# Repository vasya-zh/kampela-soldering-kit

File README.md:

# kampela-soldering-kit

## Overview

Do-it-yourself kit to make your own, fully-functional Kampela signer

## Features
- Easy to solder and self-assembly transaction signer kit
- NFC-powered batteryless operation
- secure vault implemented in EFM32PG23 MCU
- 2.7" ePaper display with touchscreen
- you can fill the assembled kit with transparent UV-cured glue after assembly and tests to make it unchangeable

## Why did we create this?

We want to make kampela design as transparent, verifiable and open-source as possible, that's simple.

## Components

Kampela solder kit consists of several off-the-shelf modules, simple electronic components and 3d printed parts:

**Modules:**
- 1pc - [Lisko A1](https://github.com/vasya-zh/Lisko) EFM32 devboard
- 1pc - [SparkFun BabyBuck 3.3V](https://www.sparkfun.com/products/18357) - step-down converter module 
- 1pc - [Olimex BB-PWR-3608](https://www.olimex.com/Products/Breadboarding/BB-PWR-3608/open-source-hardware) - step-up converter module 12V/24V
- 1pc - [Touch-6pin-adapter](https://github.com/vasya-zh/kampela-soldering-kit/tree/v2/kicad/touch-6pin-adapter) - 6-pin 0.5mm pitch FPC cable adapter for i2c touch screens
- 1pc - [NFC tag](https://github.com/vasya-zh/kampela-soldering-kit/tree/v2/kicad/tag) PCB with M24SR02 NFC EEPROM chip onboard

**PCBs:**
- 1pc - [Base-board](kicad/base-board/) - main Kampela soldering kit PCB
- 1pc - [flex nfc antenna](https://github.com/vasya-zh/kampela-soldering-kit/tree/v2/kicad/flex-coil8/production) PCB

**3d printed parts:**
- 1pc - [Solder kit enclosure](3d-models/solder-kit-enclosure.stl), 3d printed with transparent SLA resin
- 1pc - [NFC tag enclosure](3d-models/nfc-tag-enclosure.stl), 3d printed with transparent SLA resin

**Electronic components:**
- 1pc - [GDEY027T91-T01](https://www.good-display.com/product/259.html) ePaper display
- 1pc - [TLC372IP](https://www.ti.com/lit/ds/symlink/tlc372.pdf?ts=1715700121988&ref_url=https%253A%252F%252Fwww.google.com%252F) - comparator in DIP8 package
- 1pc - [L78L24](https://www.st.com/resource/en/datasheet/l78l.pdf) - 24V linear voltage regulator in TO-92 package 
- 6pcs - [1N5819](https://www.vishay.com/docs/88525/1n5817.pdf) schottky diode 40V 1A
- 1pc - [1N4743A](https://www.nexperia.com/products/diodes/zener-diodes/1N4743A.html) 13V 1W Zener diode
- 1pc - [3mm red LED](https://www.mouser.fi/ProductDetail/Vishay-Semiconductors/TLDR4900?qs=Lv5%252BaqTFJEN9M2YxsERGfA%3D%3D) for NFC field presence indication 

**Capacitors:**
- 1pc - [15pF 50V](https://www.lcsc.com/product-detail/Multilayer-Ceramic-Capacitors-MLCC-Leaded_TORCH-CC4-0805-CG-50V-15pF-J_C123158.html) ceramic capacitor
- 2pcs - [100pF 50V](https://www.lcsc.com/product-detail/Multilayer-Ceramic-Capacitors-MLCC-Leaded_Murata-Electronics-RCE5C2A101J0DBH03A_C1622101.html) ceramic capacitor
- 2pcs - [0.1uF 50V](https://www.lcsc.com/product-detail/Multilayer-Ceramic-Capacitors-MLCC-Leaded_KNSCHA-178MU0006_C5632430.html) ceramic capacitor
- 2pcs - [1uF 50V](https://www.lcsc.com/product-detail/Multilayer-Ceramic-Capacitors-MLCC-Leaded_KNSCHA-178MU0010_C5632434.html) ceramic capacitor
- 1pc - [220uF 25V](https://www.lcsc.com/product-detail/Aluminum-Electrolytic-Capacitors-Leaded_CX-Dongguan-Chengxing-Elec-KM227M025E11RR0VH2FP0_C12450.html) aluminium capacitor d6.3mm\*11mm

**Resistors:**
- 4pcs - [10k 0.125w](https://www.lcsc.com/product-detail/Through-Hole-Resistors_VO-MF1-8W-10K-1-ST26_C2903381.html) resistor
- 6pcs - [47k 0.125w](https://www.lcsc.com/product-detail/Through-Hole-Resistors_Futaba-Elec-RNU18F4702A520NH_C274421.html) resistor
- 1pc - [300k 0.125w](https://www.lcsc.com/product-detail/Through-Hole-Resistors_TyoHM-RN-1-8W-300K-F-T-B-A1_C433482.html) resistor

Complete CSV BOM can be found [here](docs/kampela-soldering-kit-BOM.csv)

## Assembly instructions

Assembly instructions can be found here: [/docs/assembly-manual.md](docs/assembly-manual.md)

> [!Note] 
> Don't fill your assembly with transparent UV adhesive before you fully test it and flash it with the right firmware.  

## Flashing and testing

Flashing and testing instructions can be found here: [/docs/flashing-n-testing.md](docs/flashing-n-testing.md)

## Using your Kampela Solder Kit

You can use your solder kit as a transaction signer with the real [Kampela firmware](https://github.com/Kalapaja/kampela-firmware)

To do that you need to flash it with the latest [binary firmware released](https://github.com/Kalapaja/kampela-firmware/tags) or build it from the [source code](https://github.com/Kalapaja/kampela-firmware)

Or you can make your customized version of the firmware and hardware.

## How to produce your own Kampela Solder Kit

You can get the kit in [kampe.la](https://kampe.la) shop

Or make your kit. To do that you need:
- order PCBs from your favourite PCB manufacturer. Gerber files can be found here: [base-board](https://github.com/vasya-zh/kampela-soldering-kit/tree/v2/kicad/base-board/production), [flex-antenna](https://github.com/vasya-zh/kampela-soldering-kit/tree/v2/kicad/flex-coil8/production)
- order modules and electronic components, see the [full BOM](docs/kampela-soldering-kit-BOM.csv)
- order or print enclosures with transparent SLA resin. STL and STEP files can be found [here](3d-models/)
- if you want you can also make your version of [Lisko A1](https://github.com/vasya-zh/Lisko) board and [FPC adapter](https://github.com/vasya-zh/kampela-soldering-kit/tree/v2/kicad/touch-6pin-adapter) board. Overwise contact [kampela team](https://kampe.la)

## About this design

Schematic PDF diagrams can be found [here](docs/)

KiCad projects can be found [here](kicad/)

This kit was made using only open-source tools:
- [KiCad](https://www.kicad.org/) - for schematics and PCBs
- [FreeCad](https://www.freecad.org/) - for enclosure design
- [Blender](https://www.blender.org/) - for renders and images
- [InkScape](https://inkscape.org/) - for instructions diagrams

## TODO
- ! Change ePaper and touch screen RESET signal polarity in test and release firmware! 

## Contributors

- [Vasilii Zhuravskii](https://github.com/vasya-zh) - solder kit v2 design, schematics, boards design, DFM, docs, tests

- [Yuri Ilin](https://www.youtube.com/@katsuk) - solder kit v1 design, schematics, flasher firmware, EFM32 test firmware in C with E-INK and other features

This project was made at [Alzymologist Oy](https://github.com/alzymologist) as a part of [Kampela](https://kampe.la) project.

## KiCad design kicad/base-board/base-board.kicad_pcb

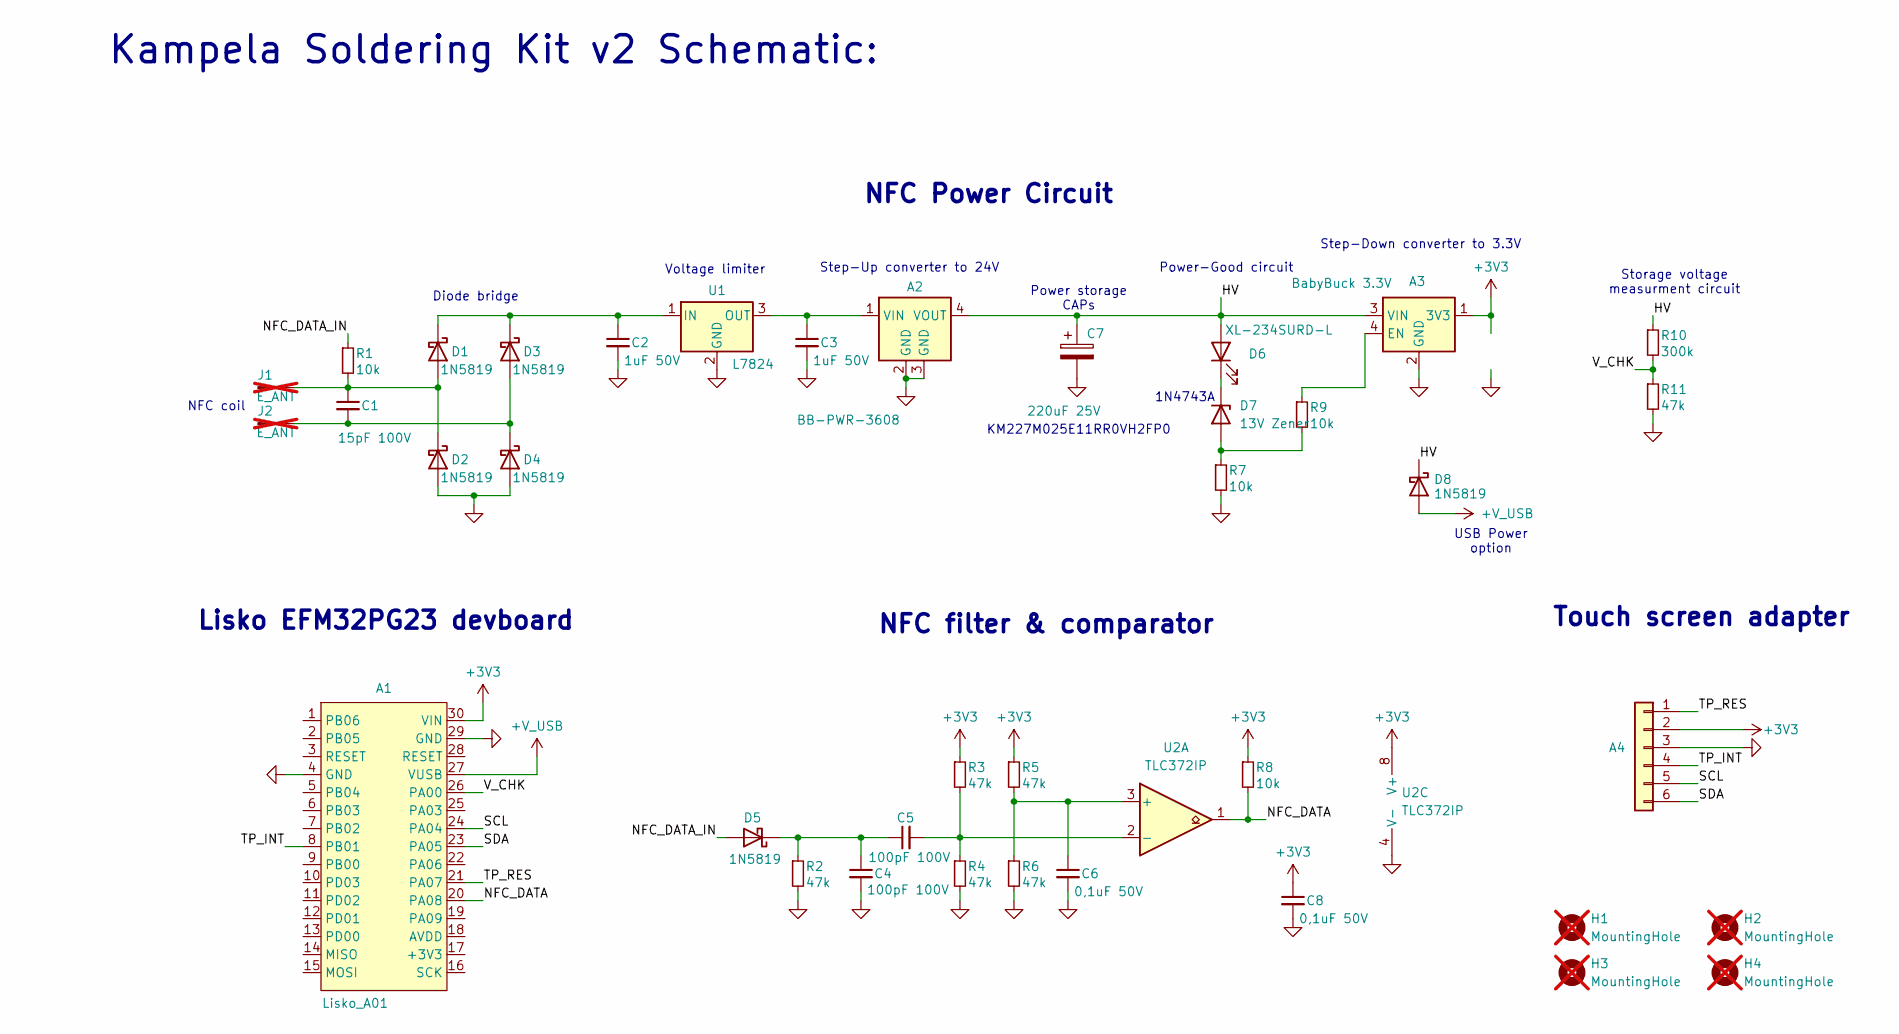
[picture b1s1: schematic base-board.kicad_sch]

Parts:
A1: Lisko_A01; Lisko_A01-DIP-only
A2: BB-PWR-3608; BB-PWR-3608-in-board
A3: BabyBuck 3.3V; SparkFun_BabyBuck_3.3V-in-board
A4: touch-6pin-adapter
C1: 15pF 100V; C_Disc_D5.0mm_W2.5mm_P2.50mm; Mouser Part # 80-C315C150J1G; LCSC Part # C123158
C2, C3: 1uF 50V; C_Disc_D5.0mm_W2.5mm_P2.50mm; Mouser Part # 81-RCER72A105K2DBH3A; LCSC Part # C5632434
C4, C5: 100pF 100V; C_Disc_D5.0mm_W2.5mm_P2.50mm; Mouser Part # 810-FG18C0G2A101JNT6; LCSC Part # C1622101
C6, C8: 0,1uF 50V; C_Disc_D5.0mm_W2.5mm_P2.50mm; Mouser Part # 80-C320C104K2R5TA; LCSC Part # C5632430
C7: 220uF 25V; CAP_RADIAL_6.3_2.5_11_HOR-DIP; Mouser Part # 710-860010473011; LCSC Part # C12450
D1, D2, D3, D4, D5, D8: 1N5819; D_DO-41_SOD81_P7.62mm_Horizontal; Mouser Part # 637-1N5819; LCSC Part # C2474
D6: XL-234SURD-L; LED_Rectangular_W3.0mm_H2.0mm; Mouser Part # 604-WP424IDT; LCSC Part # C5440555
D7: 13V Zener; D_DO-41_SOD81_P7.62mm_Horizontal; Mouser Part # 771-1N4743A-T/R; LCSC Part # C2546
H1, H2, H3, H4: MountingHole; MountingHole_2.1mm; not fitted
J1, J2: E_ANT; Pad_1.8x3; not fitted
R1, R7, R8, R9: 10k; R_Axial_DIN0204_L3.6mm_D1.6mm_P5.08mm_Horizontal; Mouser Part # 303-MF0W8FF1002A20; LCSC Part # C2903381
R2, R3, R4, R5, R6, R11: 47k; R_Axial_DIN0204_L3.6mm_D1.6mm_P5.08mm_Horizontal; Mouser Part # 303-MF0W8FF4702B00; LCSC Part # C274421
R10: 300k; R_Axial_DIN0204_L3.6mm_D1.6mm_P5.08mm_Horizontal; Mouser Part # 71-RN55E3003B; LCSC Part # C433482
U1: L7824; TO-92_Inline; Mouser Part # 863-MC79L24ACPRMG; LCSC Part # C903167
U2: TLC372IP; DIP-8_W7.62mm; Mouser Part # 595-TLC372IP; LCSC Part # C2862094

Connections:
+3V3: A1.30 (VIN), A3.1 (3V3), A4.2, C8.1, R3.1, R5.1, R8.1, U2.8 (V+)
+V_USB: A1.27 (VUSB), D8.2 (A)
/HV: A2.4 (VOUT), A3.3 (VIN), C7.1, D6.2 (A), D8.1 (K), R10.1
/NFC_DATA: A1.20 (PA08), R8.2, U2.1
/NFC_DATA_IN: D5.2 (A), R1.1
/SCL: A1.24 (PA04), A4.5
/SDA: A1.23 (PA05), A4.6
/TP_INT: A1.8 (PB01), A4.4
/TP_RES: A1.21 (PA07), A4.1
/V_CHK: A1.26 (PA00), R10.2, R11.1
GND: A1.4 (GND), A1.29 (GND), A2.2 (GND), A2.3 (GND), A3.2 (GND), A4.3, C2.2, C3.2, C4.2, C6.2, C7.2, C8.2, D2.2 (A), D4.2 (A), R2.2, R4.2, R6.2, R7.2, R11.2, U1.2 (GND), U2.4 (V-)
unnamed: A2.1 (VIN), C3.1, U1.3 (OUT)
unnamed: A3.4 (EN), R9.1
unnamed: C1.1, D1.2 (A), D2.1 (K), J1.1, R1.2
unnamed: C2.1, D1.1 (K), D3.1 (K), U1.1 (IN)
unnamed: C1.2, D3.2 (A), D4.1 (K), J2.1
unnamed: C4.1, C5.1, D5.1 (K), R2.1
unnamed: D6.1 (K), D7.1 (K)
unnamed: D7.2 (A), R7.1, R9.2
unnamed: C6.1, R5.2, R6.1, U2.3 (+)
unnamed: C5.2, R3.2, R4.1, U2.2 (-)

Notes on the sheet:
1N4743A
Lisko EFM32PG23 devboard
Kampela Soldering Kit v2 Schematic:
NFC Power Circuit
Step-Down converter to 3.3V
KM227M025E11RR0VH2FP0
USB Power option
NFC filter & comparator
Voltage limiter
Storage voltage measurment circuit
Diode bridge
Touch screen adapter
NFC coil
Step-Up converter to 24V
Power-Good circuit
Power storage CAPs

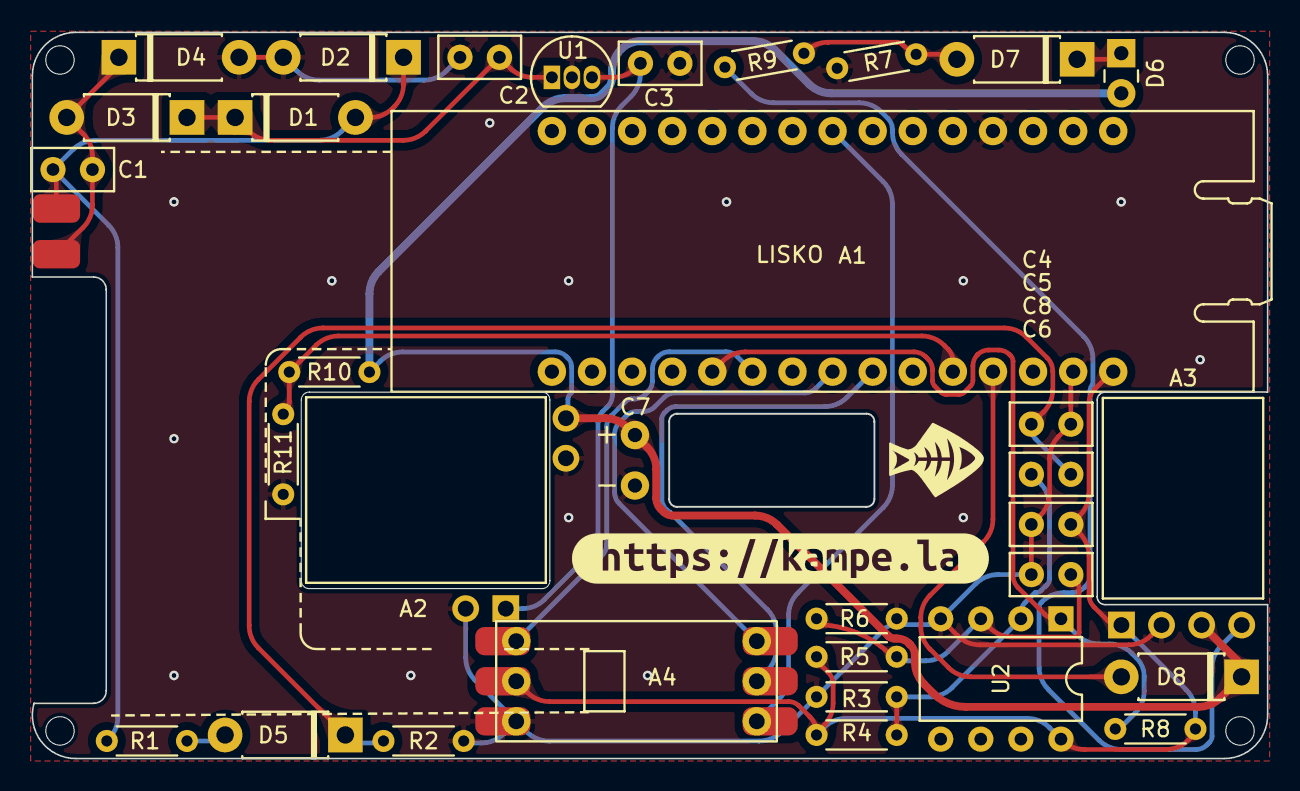
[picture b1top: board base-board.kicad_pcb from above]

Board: 2 copper layers, 78.2 x 46.0 mm, 43 parts (0 on the bottom side), 21 nets.

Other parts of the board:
H2#2, H3#2, H4#2: MountingHole; MountingHole_2.1mm
kibuzzard-6635354C: G***; kibuzzard-6635354C

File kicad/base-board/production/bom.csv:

Designator,Footprint,Quantity,Value,LCSC Part #
A1,Lisko_A01-DIP-only,1,Lisko_A01,-
A2,BB-PWR-3608-in-board,1,BB-PWR-3608,-
A3,SparkFun_BabyBuck_3.3V-in-board,1,BabyBuck 3.3V,-
A4,touch-6pin-adapter,1, ,-
C1,C_Disc_D5.0mm_W2.5mm_P2.50mm,1,15pF 100V,C123158
"C2, C3",C_Disc_D5.0mm_W2.5mm_P2.50mm,2,1uF 50V,C5632434
"C4, C5",C_Disc_D5.0mm_W2.5mm_P2.50mm,2,100pF 100V,C1622101
"C6, C8",C_Disc_D5.0mm_W2.5mm_P2.50mm,2,"0,1uF 50V",C5632430
C7,CAP_RADIAL_6.3_2.5_11_HOR-DIP,1,220uF 25V,C12450
"D1, D2, D3, D4, D5, D8",D_DO-41_SOD81_P7.62mm_Horizontal,6,1N5819,C2474
D6,LED_Rectangular_W3.0mm_H2.0mm,1,XL-234SURD-L,C5440555
D7,D_DO-41_SOD81_P7.62mm_Horizontal,1,13V Zener,C2546
"J1, J2",Pad_1.8x3,2,E_ANT,-
"R1, R7, R8, R9",R_Axial_DIN0204_L3.6mm_D1.6mm_P5.08mm_Horizontal,4,10k,C2903381
R10,R_Axial_DIN0204_L3.6mm_D1.6mm_P5.08mm_Horizontal,1,300k,C433482
"R11, R2, R3, R4, R5, R6",R_Axial_DIN0204_L3.6mm_D1.6mm_P5.08mm_Horizontal,6,47k,C274421
U1,TO-92_Inline,1,L7824,C903167
U2,DIP-8_W7.62mm,1,TLC372IP,C2862094

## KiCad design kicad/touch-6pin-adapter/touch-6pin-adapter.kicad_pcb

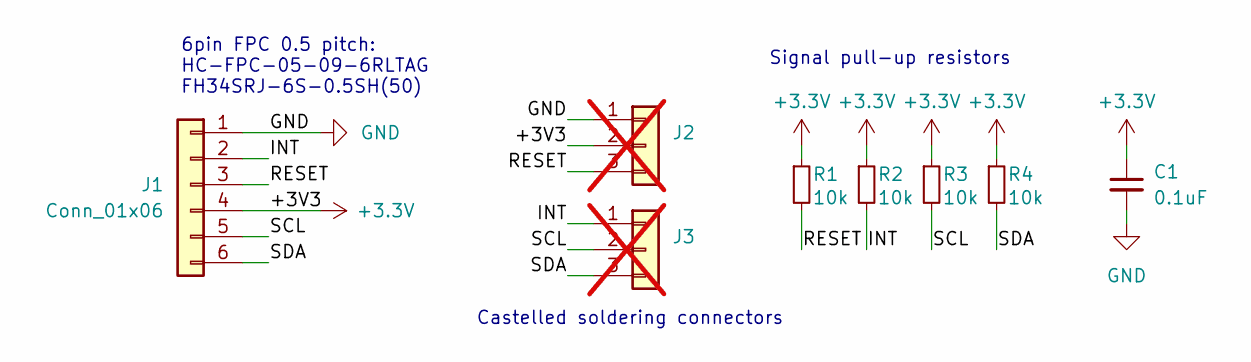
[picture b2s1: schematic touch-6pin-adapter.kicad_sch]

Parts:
C1: 0.1uF; C_0402_1005Metric; LCSC Part # C5142567
J1: Conn_01x06; HRS_FH34SRJ-6S-0.5SH_50_; LCSC Part # C5213748
J2, J3: Conn_01x03; Connector_Castelled_3pin_2.54mm_withVIA; not fitted
R1, R2, R3, R4: 10k; R_0402_1005Metric; LCSC Part # C2906885

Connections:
+3.3V: C1.1, J1.4, J2.2, R1.1, R2.1, R3.1, R4.1
/INT: J1.2, J3.1, R2.2
/RESET: J1.3, J2.3, R1.2
/SCL: J1.5, J3.2, R3.2
/SDA: J1.6, J3.3, R4.2
GND: C1.2, J1.1, J2.1

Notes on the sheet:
Signal pull-up resistors
6pin FPC 0.5 pitch: HC-FPC-05-09-6RLTAG FH34SRJ-6S-0.5SH(50)
Castelled soldering connectors

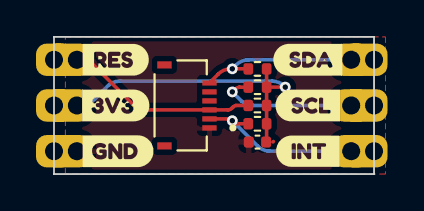
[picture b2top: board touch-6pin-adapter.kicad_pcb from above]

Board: 2 copper layers, 17.8 x 7.6 mm, 14 parts (0 on the bottom side), 6 nets.

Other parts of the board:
kibuzzard-663390A2: G***; kibuzzard-663390A2
kibuzzard-663390A9: G***; kibuzzard-663390A9
kibuzzard-663390E6: G***; kibuzzard-663390E6
kibuzzard-6633914E: G***; kibuzzard-6633914E
kibuzzard-66339095: G***; kibuzzard-66339095
kibuzzard-66339126: G***; kibuzzard-66339126

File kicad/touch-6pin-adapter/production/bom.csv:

Designator,Footprint,Quantity,Value,LCSC Part #
C1,0402,1,0.1uF,C5142567
J1,HRS_FH34SRJ-6S-0.5SH_50_,1,Conn_01x06,C5213748
"J2, J3",Connector_Castelled_3pin_2.54mm_withVIA,2,Conn_01x03,
"R1, R2, R3, R4",0402,4,10k,C2906885

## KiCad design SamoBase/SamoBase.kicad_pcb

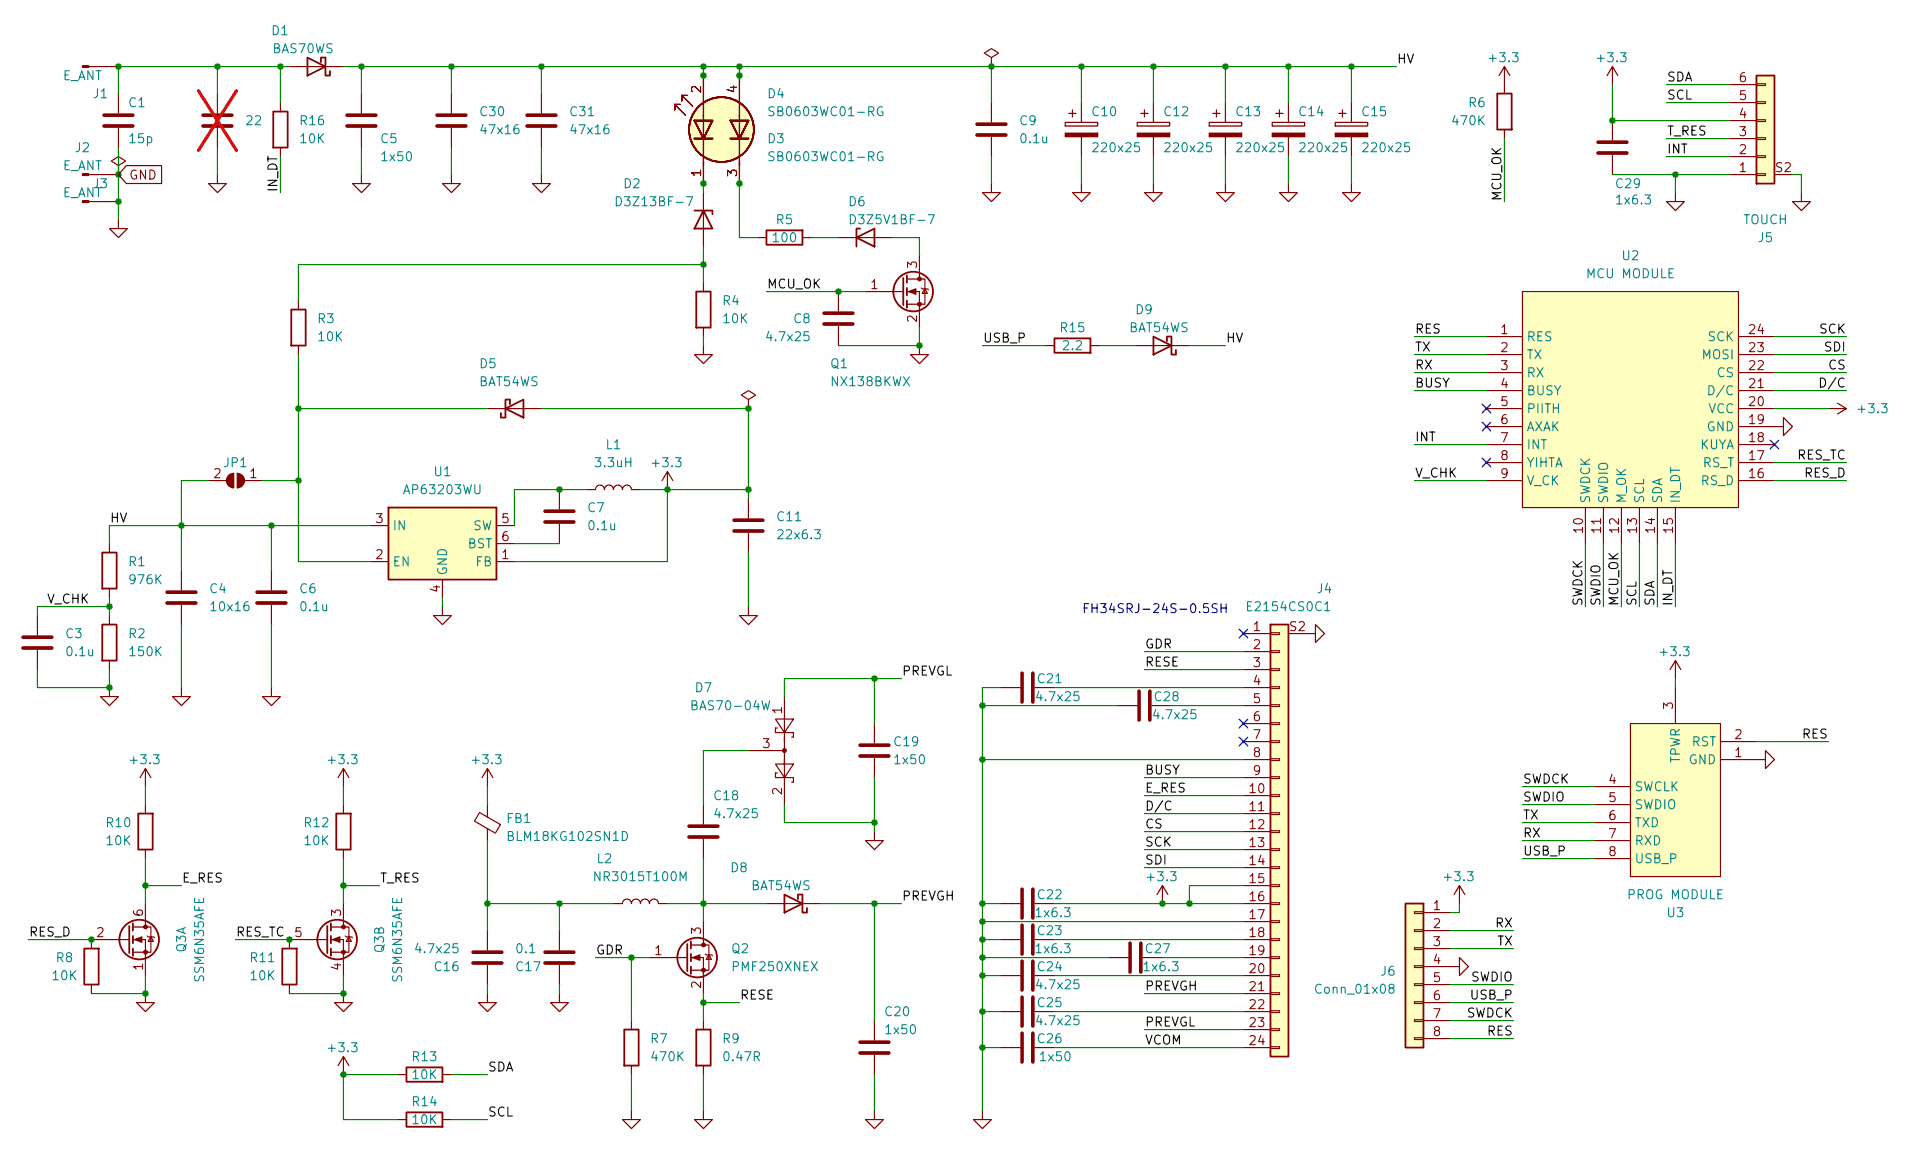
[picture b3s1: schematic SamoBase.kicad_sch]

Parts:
C1: 15p; C_0603_1608Metric
C2: 22; C_0603_1608Metric; not fitted
C3, C6, C7, C9: 0.1u; C_0402_1005Metric
C4: 10x16; C_0603_1608Metric
C5, C19, C20, C26: 1x50; C_0402_1005Metric
C8, C18: 4.7x25; C_0402_1005Metric
C10, C12, C13, C14, C15: 220x25; CAP_RADIAL_6.3_2.5_11_HOR
C11: 22x6.3; C_0603_1608Metric
C16, C21, C24, C25, C28: 4.7x25; C_0603_1608Metric
C17: 0.1; C_0402_1005Metric
C22, C23, C27, C29: 1x6.3; C_0402_1005Metric
C30, C31: 47x16; C_1210_3225Metric
D1: BAS70WS; D_SOD-323F
D2: D3Z13BF-7; D_SOD-323F
D3, D4: SB0603WC01-RG; LED_DUAL_0603
D5, D8, D9: BAT54WS; D_SOD-323F
D6: D3Z5V1BF-7; D_SOD-323F
D7: BAS70-04W; SOT-323_SC-70
FB1: BLM18KG102SN1D; L_0603_1608Metric
J1, J2, J3: E_ANT; TestPoint_Pad_2.4x3.5mm
J4: E2154CS0C1; GDEY027T91-T01_bended
J5: TOUCH; HRS_FH34SRJ-6S-0.5SH(50)
J6: Conn_01x08; PinHeader_1x08_P1.27mm_Vertical
JP1: SolderJumper_2_Open; SolderJumper_0.8.x1mm
L1: 3.3uH; L_Wuerth_MAPI-3015
L2: NR3015T100M; L_Wuerth_MAPI-3015
Q1: NX138BKWX; SOT-323_SC-70
Q2: PMF250XNEX; SOT-323_SC-70
Q3: SSM6N35AFE; SOT-563
R1: 976K; R_0402_1005Metric
R2: 150K; R_0402_1005Metric
R3, R4, R8, R10, R11, R12, R13, R14, R16: 10K; R_0402_1005Metric
R5: 100; R_0402_1005Metric
R6, R7: 470K; R_0402_1005Metric
R9: 0.47R; R_0603_1608Metric
R15: 2.2; R_0603_1608Metric
U1: AP63203WU; TSOT-23-6
U2: MCU MODULE; SamoKamp_MCU
U3: PROG MODULE; SamoKamp_Prog

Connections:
+3.3: C11.2, C22.2, C29.1, D5.2 (A), FB1.2, J4.15, J4.16, J5.4, J6.1, L1.2, R6.1, R10.2, R12.2, R13.1, R14.1, U1.1 (FB), U2.20 (VCC), U3.3 (TPWR)
/BUSY: J4.9, U2.4 (BUSY)
/CS: J4.12, U2.22 (CS)
/D/C: J4.11, U2.21 (D/C)
/E_RES: J4.10, Q3.6 (D), R10.1
/GDR: J4.2, Q2.1 (G), R7.1
/HV: C4.2, C5.1, C6.1, C9.1, C10.1, C12.1, C13.1, C14.1, C15.1, C30.2, C31.2, D1.1 (K), D3.2 (K1), D3.4 (K2), D4.2 (K1), D4.4 (K2), D9.1 (K), JP1.2 (B), R1.1, U1.3 (IN)
/INT: J5.2, U2.7 (INT)
/IN_DT: R16.2, U2.15 (IN_DT)
/MCU_OK: C8.2, Q1.1 (G), R6.2, U2.12 (M_OK)
/PREVGH: C20.1, D8.1 (K), J4.21
/PREVGL: C19.1, D7.1, J4.23
/RES: J6.8, U2.1 (RES), U3.2 (RST)
/RESE: J4.3, Q2.2 (S), R9.1
/RES_D: Q3.2 (G), R8.2, U2.16 (RS_D)
/RES_TC: Q3.5 (G), R11.2, U2.17 (RS_T)
/RX: J6.2, U2.3 (RX), U3.7 (RXD)
/SCK: J4.13, U2.24 (SCK)
/SCL: J5.5, R14.2, U2.13 (SCL)
/SDA: J5.6, R13.2, U2.14 (SDA)
/SDI: J4.14, U2.23 (MOSI)
/SWDCK: J6.7, U2.10 (SWDCK), U3.4 (SWCLK)
/SWDIO: J6.5, U2.11 (SWDIO), U3.5 (SWDIO)
/TX: J6.3, U2.2 (TX), U3.6 (TXD)
/T_RES: J5.3, Q3.3 (D), R12.1
/USB_P: J6.6, R15.1, U3.8 (USB_P)
/VCOM: C26.2, J4.24
/V_CHK: C3.1, R1.2, R2.1, U2.9 (V_CK)
GND: C1.2, C2.2, C3.2, C4.1, C5.2, C6.2, C8.1, C9.2, C10.2, C11.1, C12.2, C13.2, C14.2, C15.2, C16.1, C17.2, C19.2, C20.2, C21.1, C22.1, C23.1, C24.1, C25.1, C26.1, C27.1, C28.1, C29.2, C30.1, C31.1, D7.2, J2.1, J3.1, J4.8, J4.17, J4.S1, J4.S2 (S), J5.1, J5.S2 (S), J6.4, Q1.2 (S), Q3.1 (S), Q3.4 (S), R2.2, R4.2, R7.2, R8.1, R9.2, R11.1, U1.4 (GND), U2.19 (GND), U3.1 (GND); also elsewhere on the board
unnamed: C16.2, C17.1, FB1.1, L2.1
unnamed: C18.1, D7.3
unnamed: C1.1, C2.1, D1.2 (A), J1.1, R16.1
unnamed: D2.2 (A), R3.1, R4.1
unnamed: D2.1 (K), D3.1 (A1), D4.1 (A1)
unnamed: D3.3 (A2), D4.3 (A2), R5.1
unnamed: D5.1 (K), JP1.1 (A), R3.2, U1.2 (EN)
unnamed: D6.2 (A), Q1.3 (D)
unnamed: D6.1 (K), R5.2
unnamed: C18.2, D8.2 (A), L2.2, Q2.3 (D)
unnamed: D9.2 (A), R15.2
unnamed: C21.2, J4.4
unnamed: C28.2, J4.5
unnamed: C23.2, J4.18
unnamed: C27.2, J4.19
unnamed: C24.2, J4.20
unnamed: C25.2, J4.22
unnamed: C7.2, U1.6 (BST)
unnamed: C7.1, L1.1, U1.5 (SW)

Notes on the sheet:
FH34SRJ-24S-0.5SH

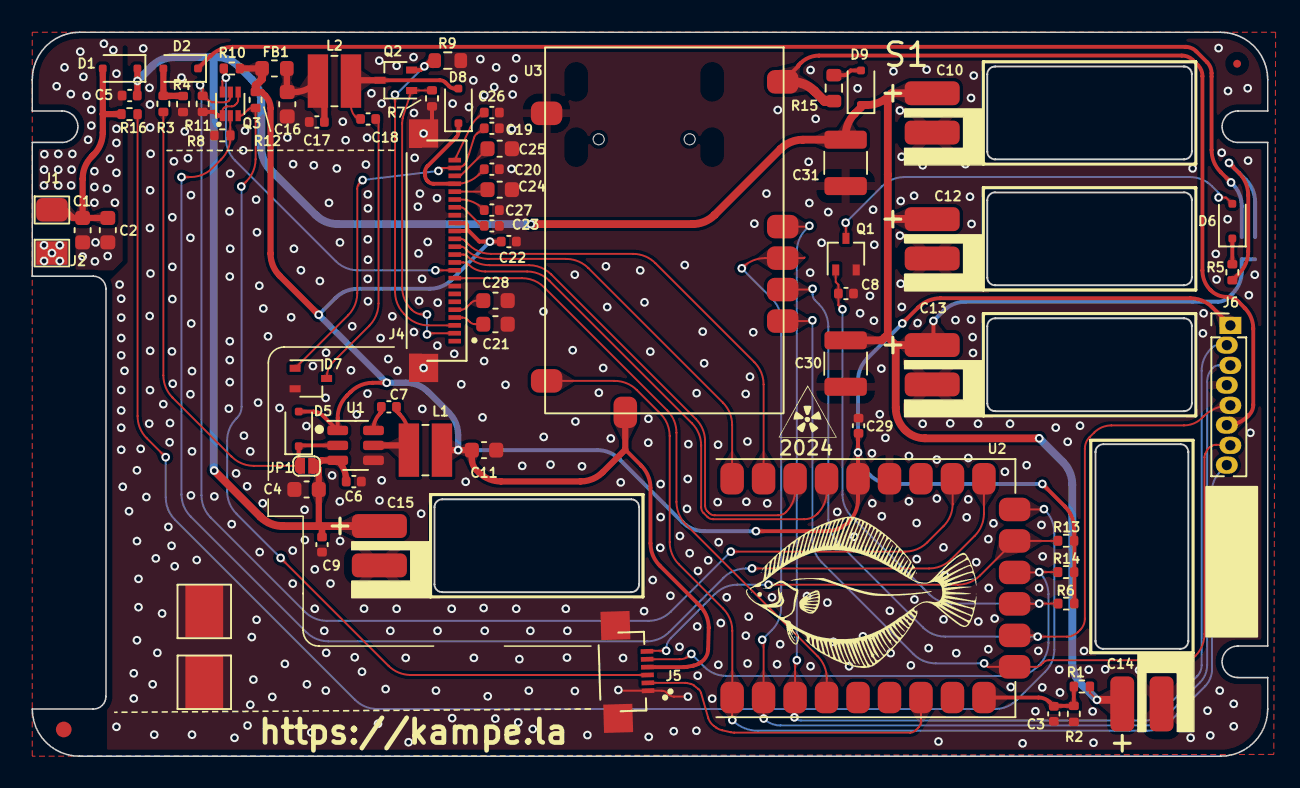
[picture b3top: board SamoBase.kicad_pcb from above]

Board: 2 copper layers, 78.5 x 46.0 mm, 74 parts (1 on the bottom side), 48 nets.

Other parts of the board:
FID1, FID4: Fiducial; Fiducial_0.5mm_Mask1.5mm
J2#2: E_ANT; TestPoint_Pad_2.4x3.5mm

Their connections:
GND: J2#2.1; also elsewhere on the board

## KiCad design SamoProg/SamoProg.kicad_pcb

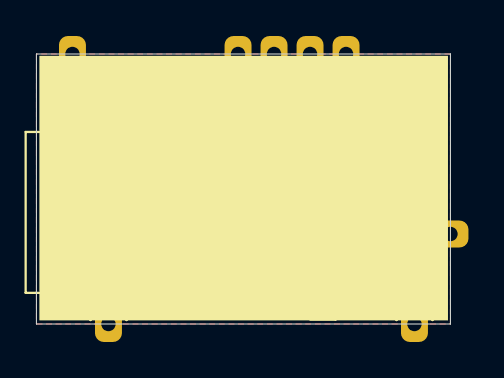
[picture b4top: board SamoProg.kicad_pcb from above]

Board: 2 copper layers, 23.0 x 15.0 mm, 46 parts (0 on the bottom side), 34 nets.

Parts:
+5V: +5; Castellated_Hole
C1, C2, C4, C7, C8, C9, C10: 0.1u; C_0402_1005Metric
C3, C6: 4.7uFx6.3; C_0603_1608Metric
D1: GREEN; LED_0402_1005Metric
D2: RED; LED_0402_1005Metric
D3: ORANGE; LED_0402_1005Metric
D4: YELLOW; LED_0402_1005Metric
FID1: Fiducial; Fiducial_0.5mm_Mask1.5mm
GND: GND; Castellated_Hole
J1: KH-TYPE-C-16P; KINGHELM_KH-TYPE-C-16P
Q1: NX138BKWX; SOT-323_SC-70
R1, R13, R14: 100; R_0402_1005Metric
R2, R3, R7, R9, R10: 5.1K; R_0402_1005Metric
R4, R5, R6, R8, R11: 10K; R_0402_1005Metric
R12, R15, R16, R17: 470; R_0402_1005Metric
RES: RES; Castellated_Hole
RX: RX; Castellated_Hole
SW1: EVQ-P2202M
SWDCK: SWDCK; Castellated_Hole
SWDIO: SWDIO; Castellated_Hole
TX: TX; Castellated_Hole
U1: NUF2042XV6; SOT-563
U3: STM32G431KBUx; QFN-32-1EP_5x5mm_P0.5mm_EP3.45x3.45mm
U4: AP2127N-3.3TRG1; SOT-23
VCC: P_SNS; Castellated_Hole
Y1: CSTNE20M; Resonator_SMD_Murata_CSTxExxV-3Pin_3.0x1.1mm

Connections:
3V3: C6.2, C7.1, C8.1, C10.1, R4.2, R11.1, SW1.1, U3.1 (VDD), U3.15 (VDDA), U3.17 (VDD), U4.2 (VO)
/CC1: J1.A5 (CC1), R2.2
/CC2: J1.B5 (CC2), R3.2
/D_N: U1.6, U3.21 (PA11)
/D_P: U1.4, U3.22 (PA12)
/LED0: R17.1, U3.13 (PB0)
/LED1: R15.1, U3.26 (PB3)
/LED2: R16.1, U3.27 (PB4)
/RST: R1.2, RES.1
/RXD: R10.2, RX.1
/SWCLK: R13.2, SWDCK.1
/SWDIO: R14.2, SWDIO.1
/TPWR_C: C9.1, R7.2, R8.1, U3.6 (PA1)
/TXD: R9.2, TX.1
/iRST: Q1.1 (G), U3.28 (PB5)
/iRXD: R10.1, U3.20 (PA10)
/iSWDO: R12.1, U3.12 (PA7)
/iTXD: R9.1, U3.19 (PA9)
/xSWCLK: R13.1, U3.10 (PA5)
/xSWD: R12.2, R14.1, U3.11 (PA6)
GND: C1.2, C2.2, C3.1, C4.2, C6.1, C7.2, C8.2, C9.2, C10.2, D1.1 (K), D2.1 (K), D3.1 (K), D4.1 (K), GND.1, J1.A1_B12 (GND), J1.A12_B1 (GND), J1.SH1 (SHIELD), J1.SH2 (SHIELD), J1.SH3 (SHIELD), J1.SH4 (SHIELD), Q1.2 (S), R2.1, R3.1, R5.1, R8.2, U1.2, U3.14 (VSSA), U3.16 (VSS), U3.32 (VSS), U3.33 (VSS), U4.1 (GND), Y1.2
unnamed: D1.2 (A), R11.2
unnamed: D2.2 (A), R15.2
unnamed: D3.2 (A), R16.2
unnamed: D4.2 (A), R17.2
unnamed: J1.A7 (DN1), J1.B7 (DN2), U1.1
unnamed: J1.A6 (DP1), J1.B6 (DP2), U1.3
unnamed: Q1.3 (D), R1.1, R6.1
unnamed: R5.2, SW1.2, U3.31 (PB8)
unnamed: U3.2 (PF0), Y1.1
unnamed: U3.3 (PF1), Y1.3
unnamed: C4.1, R4.1, U3.4 (PG10)
TPWR: R6.2, R7.1, VCC.1
USB_P: +5V.1, C1.1, C2.1, C3.2, J1.A4_B9 (VBUS), J1.A9_B4 (VBUS), U1.5, U4.3 (VI)

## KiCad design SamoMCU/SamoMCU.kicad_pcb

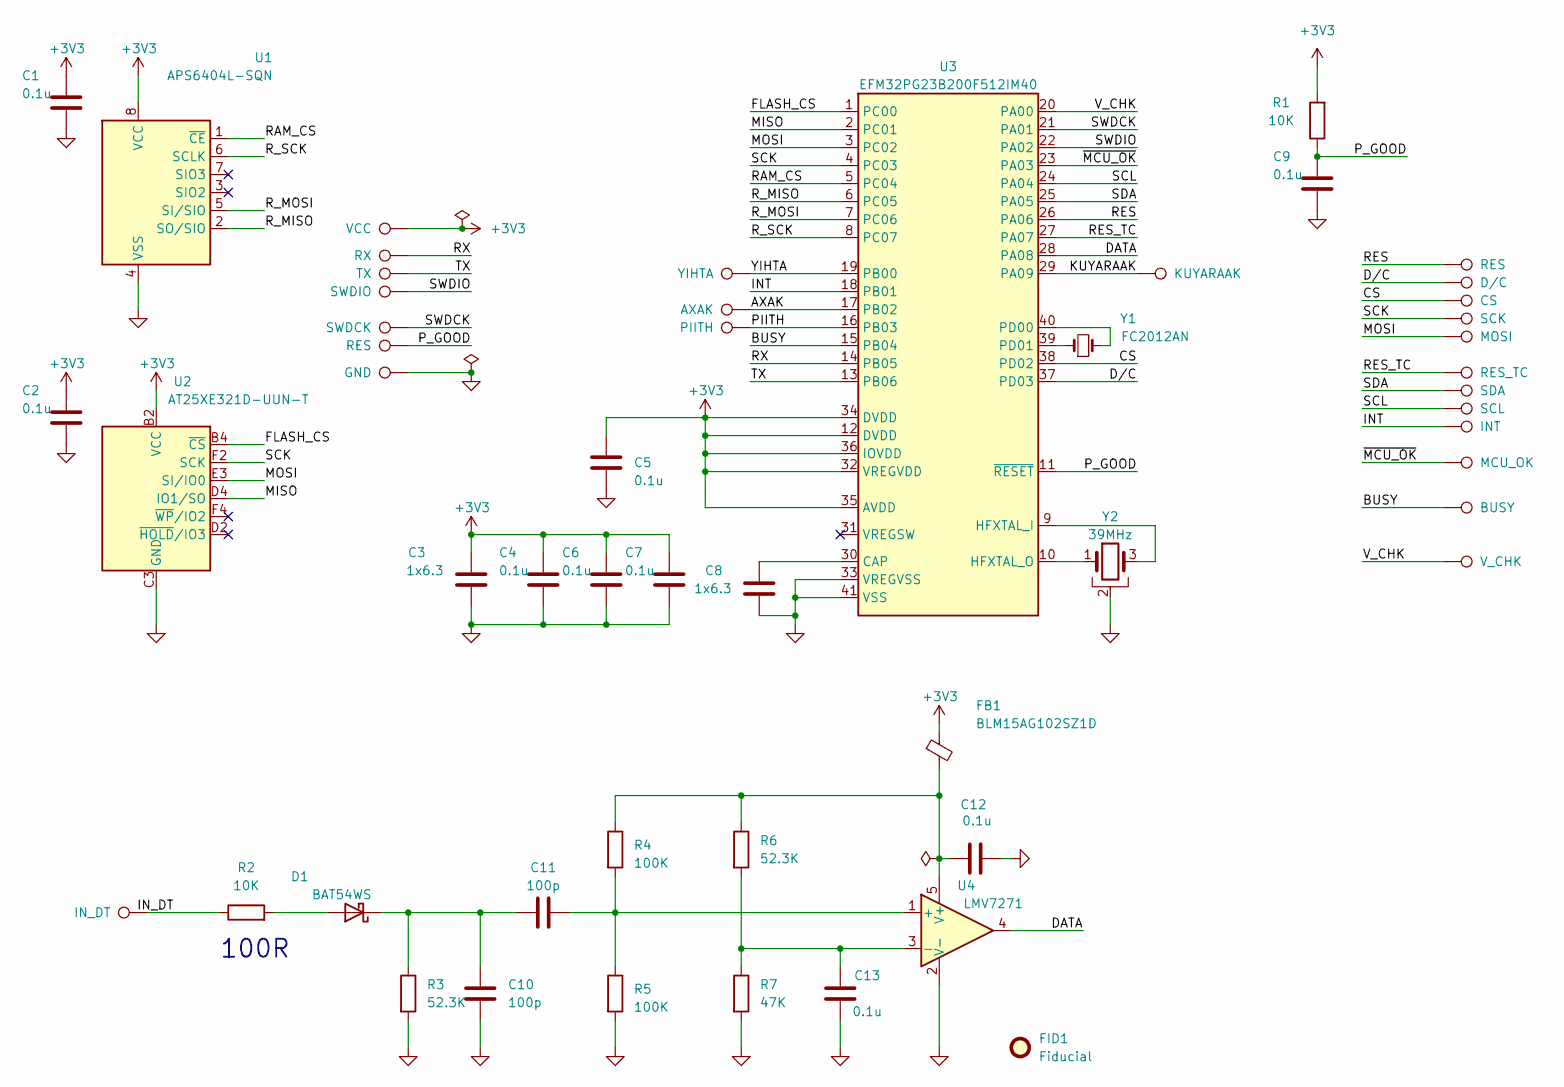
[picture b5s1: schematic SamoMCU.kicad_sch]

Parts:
AXAK1: AXAK; Castellated_Hole
BUSY1: BUSY; Castellated_Hole
C1, C2, C4, C5, C6, C7, C9, C12, C13: 0.1u; C_0402_1005Metric
C3, C8: 1x6.3; C_0402_1005Metric
C10, C11: 100p; C_0402_1005Metric
CS1: CS; Castellated_Hole
D1: BAT54WS; D_SOD-323F
D/C1: D/C; Castellated_Hole
DATA1: IN_DT; Castellated_Hole
FB1: BLM15AG102SZ1D; L_0402_1005Metric
FID1: Fiducial; Fiducial_0.5mm_Mask1.5mm
GND1: GND; Castellated_Hole
INT1: INT; Castellated_Hole
KUYARAAK1: KUYARAAK; Castellated_Hole
MCU_OK1: MCU_OK; Castellated_Hole
MOSI1: MOSI; Castellated_Hole
PIITH1: PIITH; Castellated_Hole
R1, R2: 10K; R_0402_1005Metric
R3, R6: 52.3K; R_0402_1005Metric
R4, R5: 100K; R_0402_1005Metric
R7: 47K; R_0402_1005Metric
RES1, RES2: RES; Castellated_Hole
RES_TC1: RES_TC; Castellated_Hole
RX1: RX; Castellated_Hole
SCK1: SCK; Castellated_Hole
SCL1: SCL; Castellated_Hole
SDA1: SDA; Castellated_Hole
SWDCK1: SWDCK; Castellated_Hole
SWDIO1: SWDIO; Castellated_Hole
TX1: TX; Castellated_Hole
U1: APS6404L-SQN; SON-8-1EP_3x2mm_P0.5mm_EP1.4x1.6mm
U2: AT25XE321D-UUN-T; WLCSP 12-ball 3 x 2 x 3 Array
U3: EFM32PG23B200F512IM40; QFN-40_EP_5x5_Pitch0.4mm
U4: LMV7271; SOT-353_SC-70-5
VCC1: VCC; Castellated_Hole
V_CHK1: V_CHK; Castellated_Hole
Y1: FC2012AN; Crystal_SMD_2012-2Pin_2.0x1.2mm
Y2: 39MHz; Crystal_SMD_2016-4Pin_2.0x1.6mm
YIHTA1: YIHTA; Castellated_Hole

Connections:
+3V3: C1.1, C2.1, C3.2, C4.1, C5.1, C6.1, C7.1, FB1.1, R1.2, U1.8 (VCC), U2.B2 (VCC), U3.12 (DVDD), U3.32 (VREGVDD), U3.34 (DVDD), U3.35 (AVDD), U3.36 (IOVDD), VCC1.1
/AXAK: AXAK1.1, U3.17 (PB02)
/BUSY: BUSY1.1, U3.15 (PB04)
/CS: CS1.1, U3.38 (PD02)
/DATA: U3.28 (PA08), U4.4
/D/C: D/C1.1, U3.37 (PD03)
/FLASH_CS: U2.B4 (~CS), U3.1 (PC00)
/INT: INT1.1, U3.18 (PB01)
/IN_DT: DATA1.1, R2.1
/KUYARAAK: KUYARAAK1.1, U3.29 (PA09)
/MISO: U2.D4 (IO1/SO), U3.2 (PC01)
/MOSI: MOSI1.1, U2.E3 (SI/IO0), U3.3 (PC02)
/PIITH: PIITH1.1, U3.16 (PB03)
/P_GOOD: C9.1, R1.1, RES1.1, U3.11 (~RESET)
/RAM_CS: U1.1 (~CE), U3.5 (PC04)
/RES: RES2.1, U3.26 (PA06)
/RES_TC: RES_TC1.1, U3.27 (PA07)
/RX: RX1.1, U3.14 (PB05)
/R_MISO: U1.2 (SO/SIO), U3.6 (PC05)
/R_MOSI: U1.5 (SI/SIO), U3.7 (PC06)
/R_SCK: U1.6 (SCLK), U3.8 (PC07)
/SCK: SCK1.1, U2.F2 (SCK), U3.4 (PC03)
/SCL: SCL1.1, U3.24 (PA04)
/SDA: SDA1.1, U3.25 (PA05)
/SWDCK: SWDCK1.1, U3.21 (PA01)
/SWDIO: SWDIO1.1, U3.22 (PA02)
/TX: TX1.1, U3.13 (PB06)
/V_CHK: U3.20 (PA00), V_CHK1.1
/YIHTA: U3.19 (PB00), YIHTA1.1
/~MCU_OK: MCU_OK1.1, U3.23 (PA03)
GND: C1.2, C2.2, C3.1, C4.2, C5.2, C6.2, C7.2, C8.1, C9.2, C10.2, C12.1, C13.2, GND1.1, R3.2, R5.2, R7.2, U1.4 (VSS), U2.C3 (GND), U3.33 (VREGVSS), U3.41 (VSS), U4.2 (V-), Y2.2
unnamed: D1.2 (A), R2.2
unnamed: C10.1, C11.2, D1.1 (K), R3.1
unnamed: C8.2, U3.30 (CAP)
unnamed: U3.9 (HFXTAL_I), Y2.3
unnamed: U3.10 (HFXTAL_O), Y2.1
unnamed: U3.40 (PD00), Y1.2
unnamed: U3.39 (PD01), Y1.1
unnamed: C11.1, R4.2, R5.1, U4.1 (+)
unnamed: C13.1, R6.2, R7.1, U4.3 (-)
unnamed: C12.2, FB1.2, R4.1, R6.1, U4.5 (V+)

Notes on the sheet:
100R

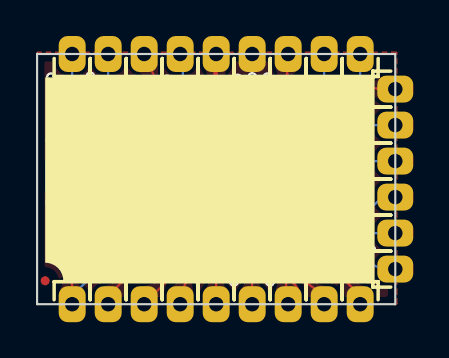
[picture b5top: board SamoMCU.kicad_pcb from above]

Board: 2 copper layers, 19.9 x 13.9 mm, 53 parts (0 on the bottom side), 41 nets.

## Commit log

2024-05-07 v1 initial commit
2024-05-07 assembly manual test commit
2024-05-07 assemblu manual test commit
2024-05-08 test
2024-05-14 kicad files added
2024-05-14 v2 clean-up and check
2024-05-14 kampela-soldering-kit-v2 (#1)
    * assembly manual test commit
    * assemblu manual test commit
    * assembly manual test commit
    * assembly manual test commit
    * assembly manual test commit
    * assembly manual test commit
2024-05-14 title-image source svg added
